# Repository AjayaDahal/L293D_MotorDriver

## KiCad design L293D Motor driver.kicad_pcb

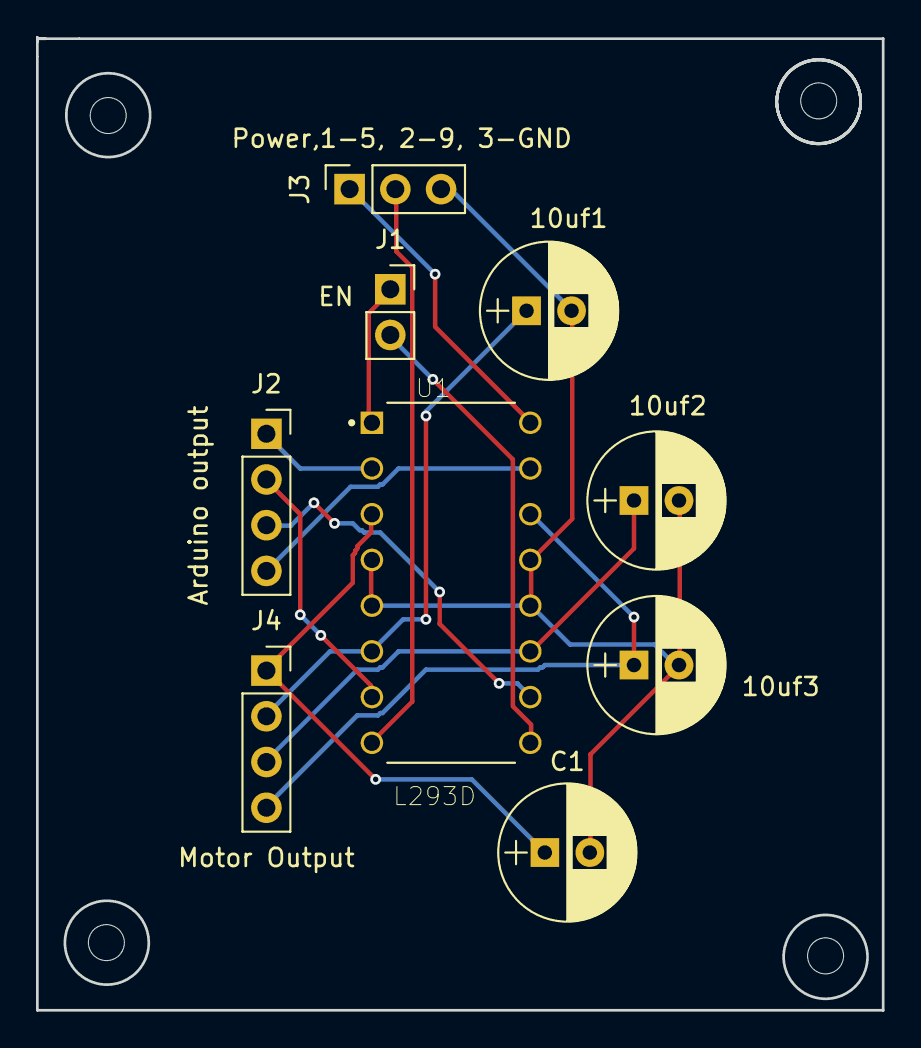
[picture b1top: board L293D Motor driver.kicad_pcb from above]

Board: 2 copper layers, 47.0 x 54.1 mm, 9 parts (0 on the bottom side), 13 nets.

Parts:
10uf1, 10uf2, 10uf3: CP; CP_Radial_D7.5mm_P2.50mm
C1: 10uf; CP_Radial_D7.5mm_P2.50mm
J1: EN; PinSocket_1x02_P2.54mm_Vertical
J2: Arduino output; PinSocket_1x04_P2.54mm_Vertical
J3: Power,1-5, 2-9, 3-GND; PinSocket_1x03_P2.54mm_Vertical
J4: Motor Output; PinSocket_1x04_P2.54mm_Vertical
U1: L293D; DIP880W50P254L2000H510Q16

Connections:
5V: J3.1, U1.16
9V: J3.2, U1.8
EN1: J1.1, U1.1
EN2: J1.2, U1.9
GND: 10uf1.2, 10uf2.2, 10uf3.2, C1.2, J3.3, U1.4, U1.5, U1.12, U1.13
Motor1A: J2.1, U1.2
Motor1AOut: C1.1, J4.1, U1.3
Motor1B: J2.2, U1.7
Motor1BOut: 10uf1.1, J4.2, U1.6
Motor2A: J2.3, U1.10
Motor2AOut: 10uf2.1, J4.3, U1.11
Motor2B: J2.4, U1.15
Motor2BOut: 10uf3.1, J4.4, U1.14
